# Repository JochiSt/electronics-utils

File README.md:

# electronics-utils

This is a collection of small breakout boards etc. that make life easier but
don't really warrant being called projects on their own. See the respective
subdirectories for more details.

Gerbers (proven with JLCPCB) live in the fab/ subdirectories.

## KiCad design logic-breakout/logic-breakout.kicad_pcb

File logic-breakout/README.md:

# logic-breakout

Solder-in adapter for cheap chinese logic analyzers follwing the quasi-standard
CH1-8 and GND pinouts. Simply solder Kynar wire to this board and your DUT.

Cheap enough to just have a bunch of and leave them attached to your DUTs,
which keeps the pin mapping clear and consistent while being able to freely
move the LA around.

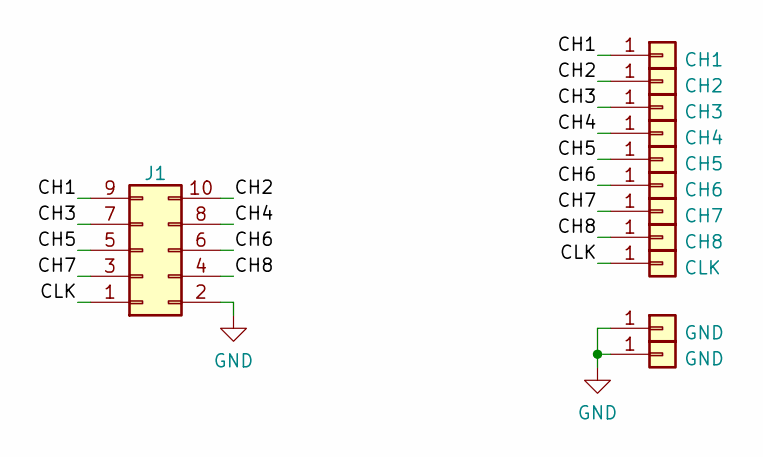
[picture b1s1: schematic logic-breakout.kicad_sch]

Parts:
J1: Conn_02x05_Odd_Even; PinHeader_2x05_P2.54mm_Vertical; MPN SFH11-PBPC-D05-RA-BK; Digikey S9202-ND
J2: CH1; SolderPoint
J3: CH2; SolderPoint
J4: CH3; SolderPoint
J5: CH4; SolderPoint
J6: CH5; SolderPoint
J7: CH6; SolderPoint
J8: CH7; SolderPoint
J9: CH8; SolderPoint
J10: CLK; SolderPoint
J11, J12: GND; SolderPoint

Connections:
/CH1: J1.9, J2.1
/CH2: J1.10, J3.1
/CH3: J1.7, J4.1
/CH4: J1.8, J5.1
/CH5: J1.5, J6.1
/CH6: J1.6, J7.1
/CH7: J1.3, J8.1
/CH8: J1.4, J9.1
/CLK: J1.1, J10.1
GND: J1.2, J11.1, J12.1

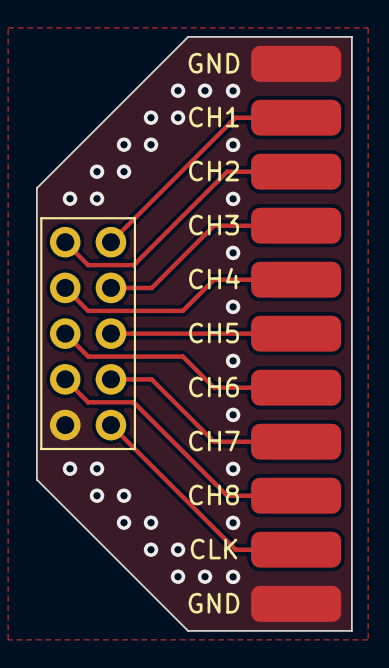
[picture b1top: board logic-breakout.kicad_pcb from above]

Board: 2 copper layers, 17.5 x 33.0 mm, 12 parts (0 on the bottom side), 10 nets.

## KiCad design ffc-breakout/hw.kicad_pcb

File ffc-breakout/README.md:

# ffc-breakout

Simple breakout for 0.5mm-pitch flat flex connectors with up to 40 pins.
Designed for the Hirose FH12 series, but works with many common models.

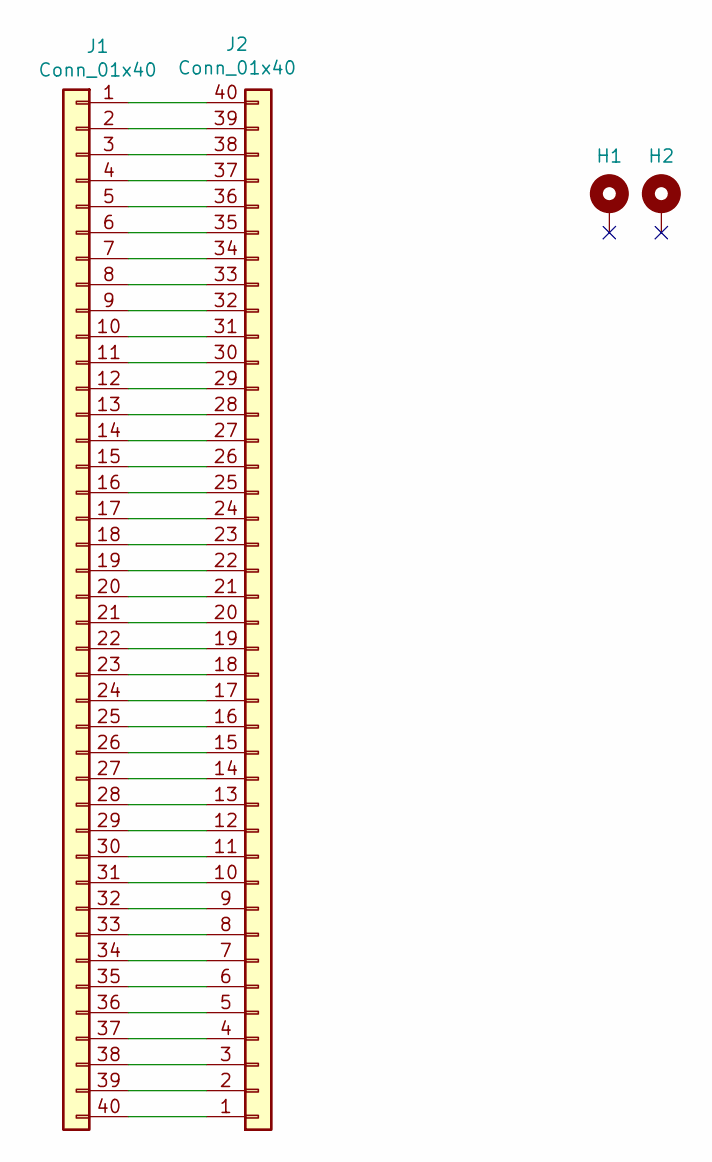
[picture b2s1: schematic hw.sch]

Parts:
H1, H2: MountingHole_Pad; MountingHole_3.2mm_M3_ISO14580_Pad
J1: Conn_01x40; Hirose_FH12-40S-0.5SH_1x40-1MP_P0.50mm_Horizontal
J2: Conn_01x40; PinHeader_2x20_P2.54mm_Vertical

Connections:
unnamed: J1.1, J2.40
unnamed: J1.2, J2.39
unnamed: J1.3, J2.38
unnamed: J1.4, J2.37
unnamed: J1.5, J2.36
unnamed: J1.6, J2.35
unnamed: J1.7, J2.34
unnamed: J1.8, J2.33
unnamed: J1.9, J2.32
unnamed: J1.10, J2.31
unnamed: J1.11, J2.30
unnamed: J1.12, J2.29
unnamed: J1.13, J2.28
unnamed: J1.14, J2.27
unnamed: J1.15, J2.26
unnamed: J1.16, J2.25
unnamed: J1.17, J2.24
unnamed: J1.18, J2.23
unnamed: J1.19, J2.22
unnamed: J1.20, J2.21
unnamed: J1.21, J2.20
unnamed: J1.22, J2.19
unnamed: J1.23, J2.18
unnamed: J1.24, J2.17
unnamed: J1.25, J2.16
unnamed: J1.26, J2.15
unnamed: J1.27, J2.14
unnamed: J1.28, J2.13
unnamed: J1.29, J2.12
unnamed: J1.30, J2.11
unnamed: J1.31, J2.10
unnamed: J1.32, J2.9
unnamed: J1.33, J2.8
unnamed: J1.34, J2.7
unnamed: J1.35, J2.6
unnamed: J1.36, J2.5
unnamed: J1.37, J2.4
unnamed: J1.38, J2.3
unnamed: J1.39, J2.2
unnamed: J1.40, J2.1

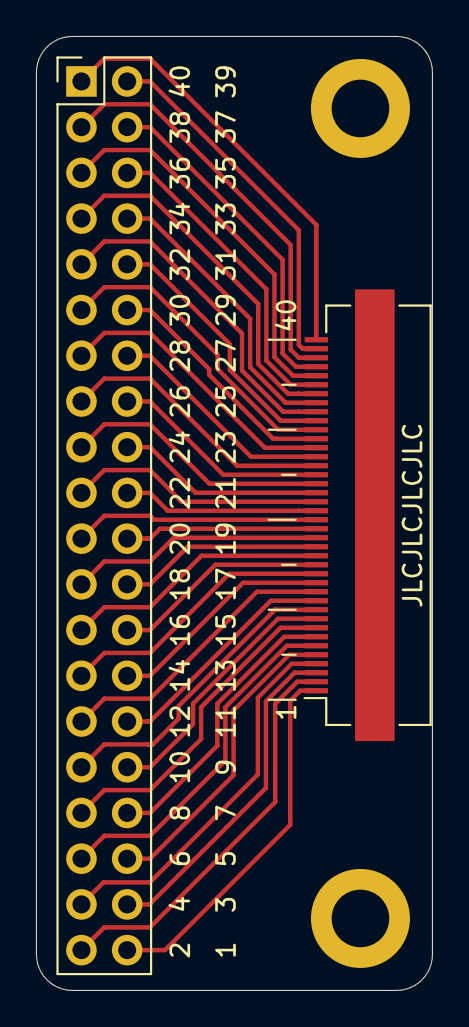
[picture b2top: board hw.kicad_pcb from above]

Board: 2 copper layers, 22.0 x 53.0 mm, 4 parts (0 on the bottom side), 40 nets.

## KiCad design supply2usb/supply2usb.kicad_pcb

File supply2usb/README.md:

# supply2usb

A board for powering USB devices from a lab supply. Useful for testing new
devices with a current-limiting safety net. No more butchering USB cables!

Fits into standard 19mm/0.75" pitch 4mm sockets.

Additional features:
 * Has holes for adding ziptie loops to make unplugging easier.
 * The resistor options allow signalling various battery charging standards if
   desired.

BOM:
 * 2× Banana plug: Pomona Electronics 72918 (Digi-Key Part Number: 501-1200-ND)
 * 1× USB socket: Cvilux CU01SAV0S00 (Digi-Key Part Number: 2987-CU01SAV0S00-ND)

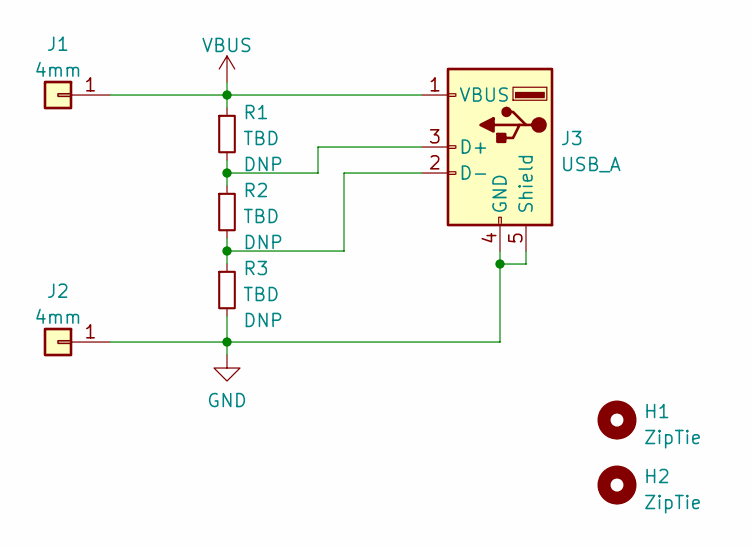
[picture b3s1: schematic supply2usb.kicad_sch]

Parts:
H1, H2: ZipTie; Ziptie_3.6mm
J1, J2: 4mm; Pomona_72918; MPN 72918; Digikey 501-1200-ND
J3: USB_A; Cvilux_CU01SAV0S00; MPN CU01SAV0S00; Digikey 2987-CU01SAV0S00-ND
R1, R2, R3: TBD; R_0603_1608Metric

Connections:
GND: J2.1, J3.4 (GND), J3.5 (Shield), R3.2
unnamed: J3.2 (D-), R2.2, R3.1
unnamed: J3.3 (D+), R1.2, R2.1
VBUS: J1.1, J3.1 (VBUS), R1.1

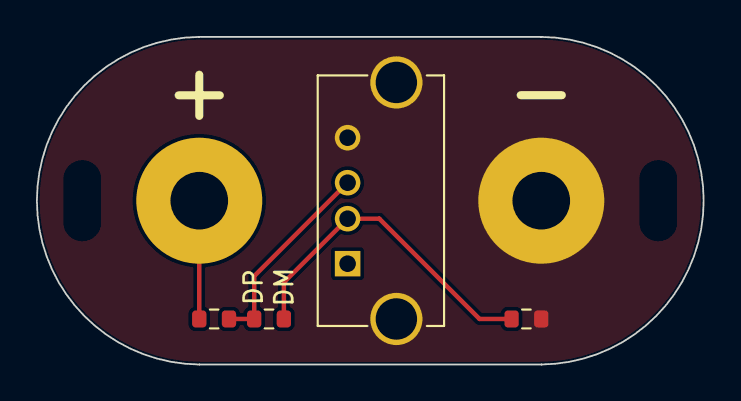
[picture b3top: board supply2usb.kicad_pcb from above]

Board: 2 copper layers, 37.0 x 18.2 mm, 8 parts (0 on the bottom side), 4 nets.

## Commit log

2022-10-29 import
2023-12-16 import ffc-breakout
    Had this lying around for ages, might as well publish it.
2023-12-16 fix typo in top-level readme
2025-05-15 updated to KiCADv9
